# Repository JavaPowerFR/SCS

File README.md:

# SCS
SCS Interface For MyHOME Products Legrand BTicino

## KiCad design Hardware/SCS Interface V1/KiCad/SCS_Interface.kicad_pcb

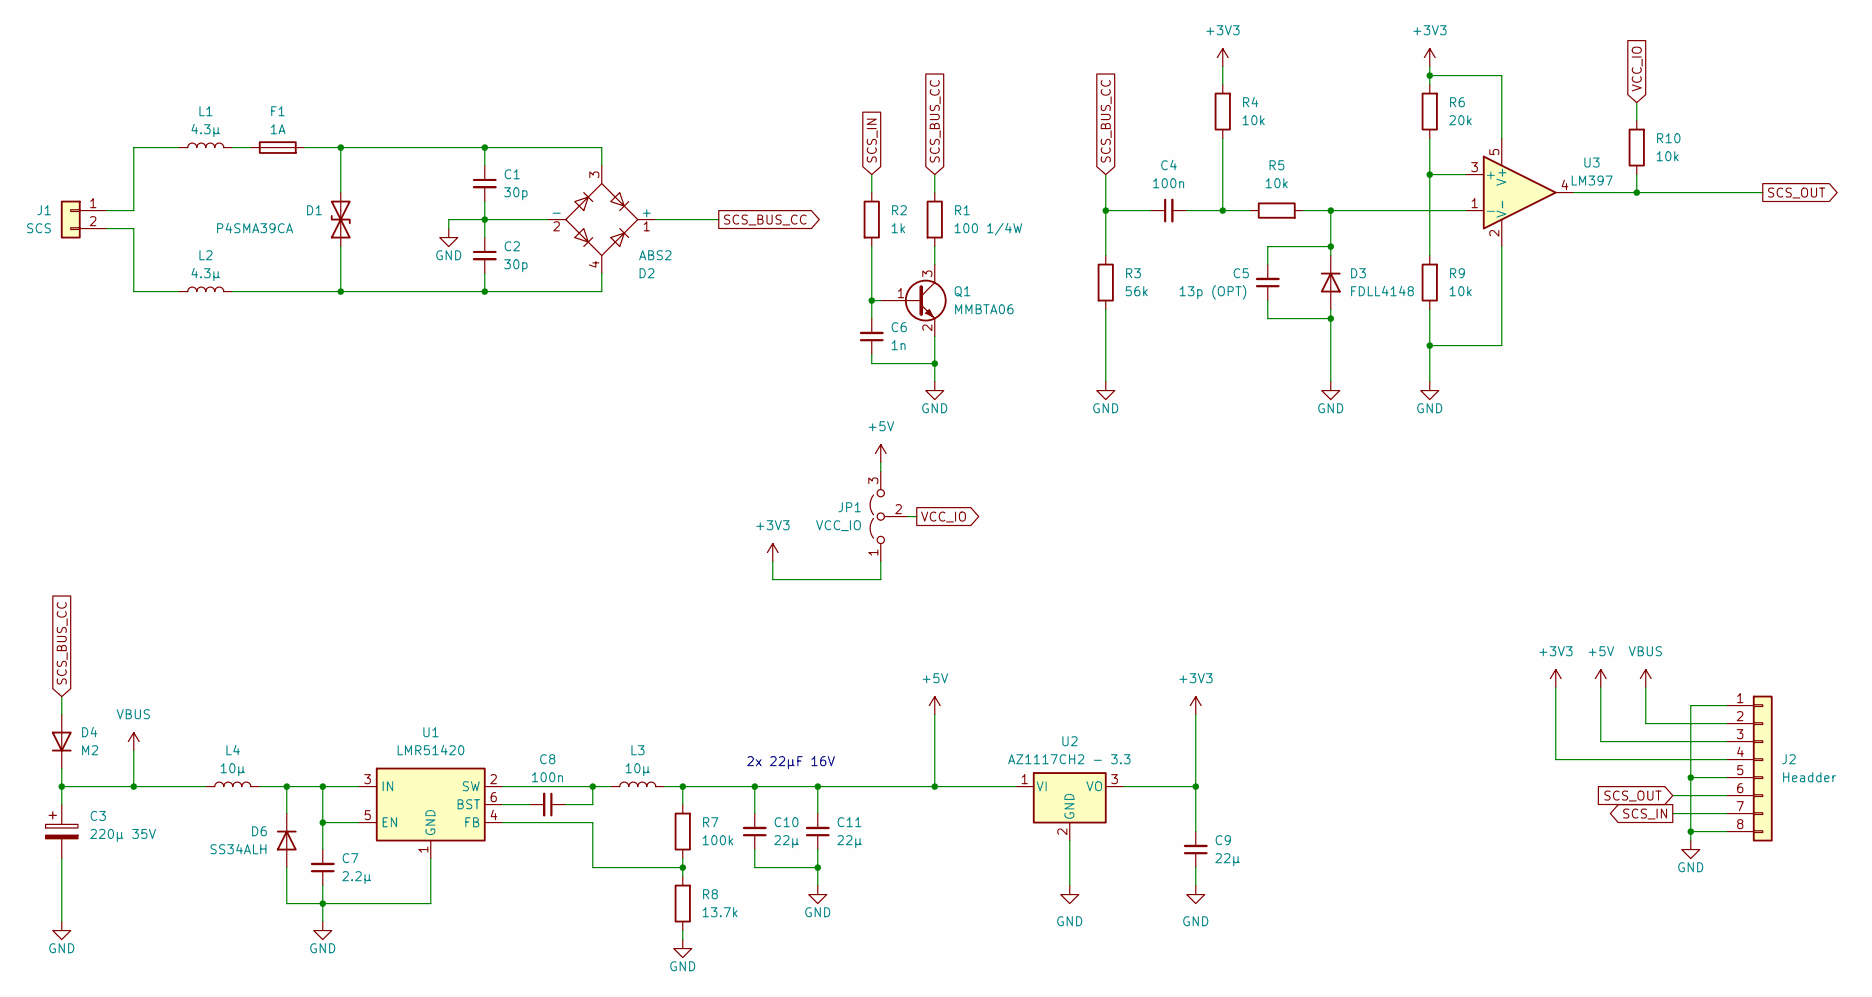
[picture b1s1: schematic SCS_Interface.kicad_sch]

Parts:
C1, C2: 30p; C_0805_2012Metric
C3: 220µ 35V; CP_Elec_8x10
C4, C8: 100n; C_0805_2012Metric
C5: 13p (OPT); C_0805_2012Metric
C6: 1n; C_0805_2012Metric
C7: 2.2µ; C_0805_2012Metric
C9, C10, C11: 22µ; C_0805_2012Metric
D1: P4SMA39CA; D_SMA
D2: ABS2; Diode_Bridge_Diotec_ABS
D3: FDLL4148; D_MiniMELF
D4: M2; D_SMA
D6: SS34ALH; D_SMA
F1: 1A; Fuse_1206_3216Metric_Pad1.42x1.75mm_HandSolder
J1: SCS; TerminalBlock_Phoenix_MKDS-1,5-2_1x02_P5.00mm_Horizontal_PNP
J2: Headder; PinHeader_1x08_P2.54mm_Vertical
JP1: VCC_IO; SolderJumper-3_P1.3mm_Open_RoundedPad1.0x1.5mm
L1, L2: 4.3µ; L_Wuerth_MAPI-3020
L3, L4: 10µ; L_Sunlord_SWPA6028S
Q1: MMBTA06; SOT-23
R1: 100 1/4W; R_1206_3216Metric
R2: 1k; R_0805_2012Metric
R3: 56k; R_0805_2012Metric
R4, R5, R9, R10: 10k; R_0805_2012Metric
R6: 20k; R_0805_2012Metric
R7: 100k; R_0805_2012Metric
R8: 13.7k; R_0805_2012Metric
U1: LMR51420; SOT-23-6
U2: AZ1117CH2 - 3.3; SOT-223-3_TabPin2
U3: LM397; SOT-23-5

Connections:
+3V3: C9.2, J2.4, JP1.1 (A), R4.2, R6.2, U2.3 (VO), U3.5 (V+)
+5V: C10.2, C11.2, J2.3, JP1.3 (B), L3.2, R7.2, U2.1 (VI)
GND: C1.2, C2.1, C3.2, C5.1, C6.1, C7.1, C9.1, C10.1, C11.1, D2.2 (-), D3.2 (A), D6.2 (A), J2.1, J2.5, J2.8, Q1.2 (E), R3.2, R8.1, R9.1, U1.1 (GND), U2.2 (GND), U3.2 (V-)
unnamed: C4.2, R4.1, R5.1
unnamed: C2.2, D1.1 (A1), D2.4, L2.2
unnamed: C1.1, D1.2 (A2), D2.3, F1.2
unnamed: C5.2, D3.1 (K), R5.2, U3.1 (-)
unnamed: C7.2, D6.1 (K), L4.2, U1.3 (IN), U1.5 (EN)
unnamed: F1.1, L1.2
unnamed: J1.1, L1.1
unnamed: J1.2, L2.1
unnamed: C6.2, Q1.1 (B), R2.2
unnamed: Q1.3 (C), R1.2
unnamed: C8.2, U1.6 (BST)
unnamed: R7.1, R8.2, U1.4 (FB)
unnamed: C8.1, L3.1, U1.2 (SW)
unnamed: R6.1, R9.2, U3.3 (+)
SCS_BUS_CC: C4.1, D2.1 (+), D4.2 (A), R1.1, R3.1
SCS_IN: J2.7, R2.1
SCS_OUT: J2.6, R10.1, U3.4
VBUS: C3.1, D4.1 (K), J2.2, L4.1
VCC_IO: JP1.2 (C), R10.2

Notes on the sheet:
2x 22µF 16V

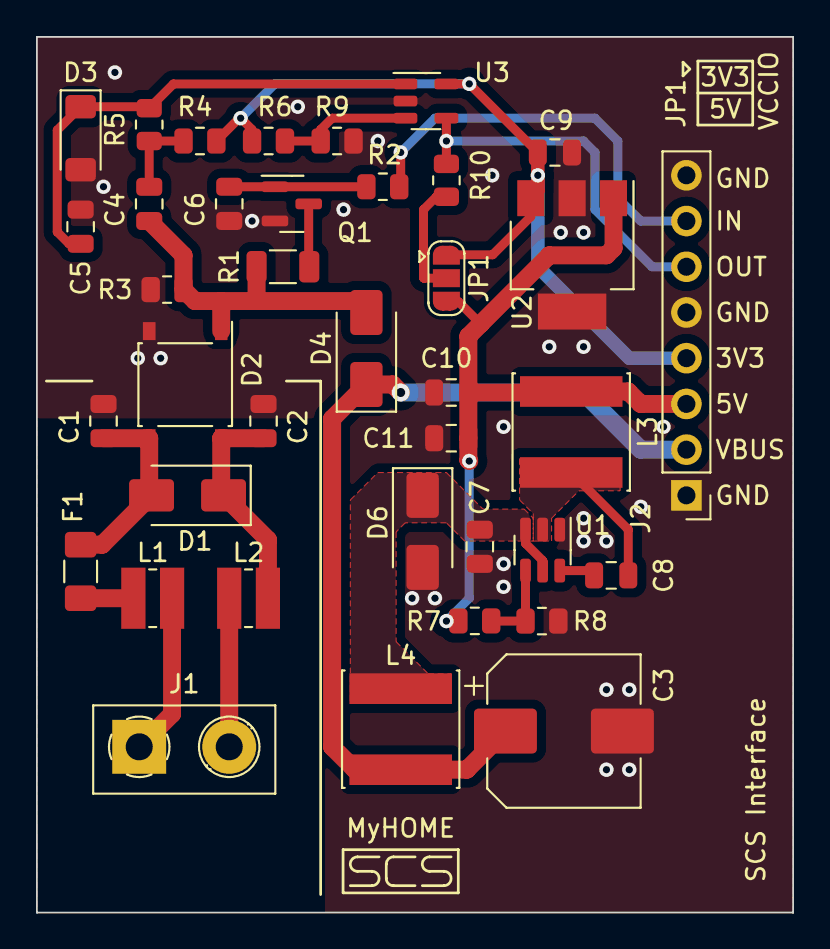
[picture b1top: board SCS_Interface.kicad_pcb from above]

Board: 2 copper layers, 42.0 x 48.6 mm, 38 parts (0 on the bottom side), 22 nets.

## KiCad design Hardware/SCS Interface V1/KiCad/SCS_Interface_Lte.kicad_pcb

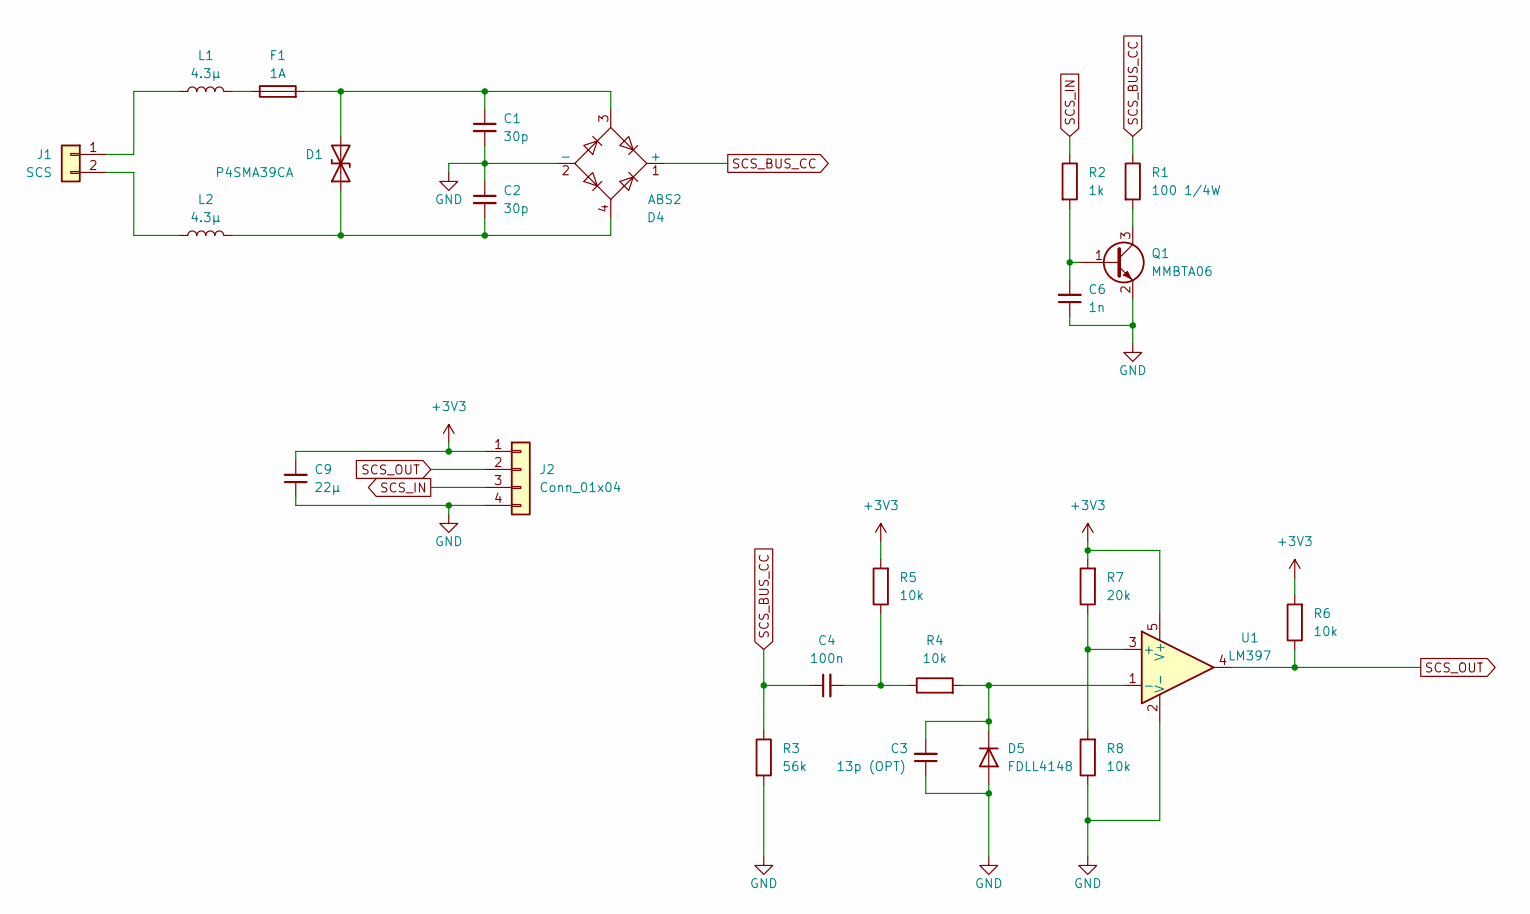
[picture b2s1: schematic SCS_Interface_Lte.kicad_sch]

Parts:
C1, C2: 30p; C_0805_2012Metric
C3: 13p (OPT); C_0805_2012Metric
C4: 100n; C_0805_2012Metric
C6: 1n; C_0805_2012Metric
C9: 22µ; C_0805_2012Metric
D1: P4SMA39CA; D_SMA
D4: ABS2; Diode_Bridge_Diotec_ABS
D5: FDLL4148; D_MiniMELF
F1: 1A; Fuse_1206_3216Metric_Pad1.42x1.75mm_HandSolder
J1: SCS; TerminalBlock_Phoenix_MKDS-1,5-2_1x02_P5.00mm_Horizontal_PNP
J2: Conn_01x04; PinHeader_1x04_P2.54mm_Vertical
L1, L2: 4.3µ; L_Wuerth_MAPI-3020
Q1: MMBTA06; SOT-23
R1: 100 1/4W; R_1206_3216Metric
R2: 1k; R_0805_2012Metric
R3: 56k; R_0805_2012Metric
R4, R5, R6, R8: 10k; R_0805_2012Metric
R7: 20k; R_0805_2012Metric
U1: LM397; SOT-23-5

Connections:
+3V3: C9.2, J2.1, R5.2, R6.2, R7.2, U1.5 (V+)
GND: C1.2, C2.1, C3.1, C6.1, C9.1, D4.2 (-), D5.2 (A), J2.4, Q1.2 (E), R3.2, R8.1, U1.2 (V-)
unnamed: C4.2, R4.1, R5.1
unnamed: C2.2, D1.1 (A1), D4.4, L2.2
unnamed: C1.1, D1.2 (A2), D4.3, F1.2
unnamed: C3.2, D5.1 (K), R4.2, U1.1 (-)
unnamed: F1.1, L1.2
unnamed: J1.1, L1.1
unnamed: J1.2, L2.1
unnamed: C6.2, Q1.1 (B), R2.2
unnamed: Q1.3 (C), R1.2
unnamed: R7.1, R8.2, U1.3 (+)
SCS_BUS_CC: C4.1, D4.1 (+), R1.1, R3.1
SCS_IN: J2.3, R2.1
SCS_OUT: J2.2, R6.1, U1.4

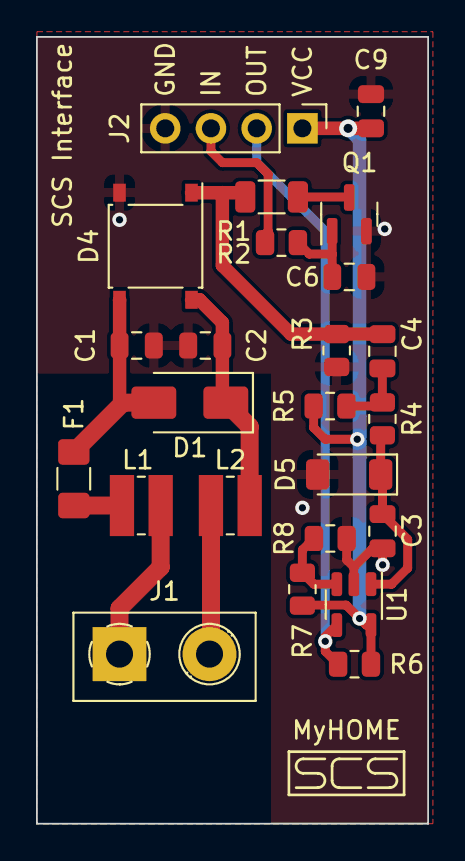
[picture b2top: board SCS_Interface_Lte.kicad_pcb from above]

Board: 2 copper layers, 21.7 x 43.7 mm, 24 parts (0 on the bottom side), 15 nets.

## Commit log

2024-05-12 PhysicalLayer
2024-05-12 Rename PhysicalLayer
2024-05-12 Doc Physical Layer Images
2024-05-12 Rename PhysicalLayer.md to 01_PhysicalLayer.md
2024-05-12 02 First Interface
2024-05-12 04 Reverse engineering
2024-05-12 Schematic Interface SCS V1
2024-05-12 Add KiCad project for scs interface V1
2024-05-12 schematic V1 test On, Breadboard
2024-05-12 Decryptor Application
2024-05-12 protocol example ON OFF
2024-05-12 Protocol timming
2024-05-30 Update PCB after first pcb build
    - Replace input detection
2024-06-03 Update SCS Decoder
2024-06-03 Resources to decode scs packets
2024-06-03 Open Web Net TCP Sniffer
2024-06-03 Add Resource MHCatalogue.db
